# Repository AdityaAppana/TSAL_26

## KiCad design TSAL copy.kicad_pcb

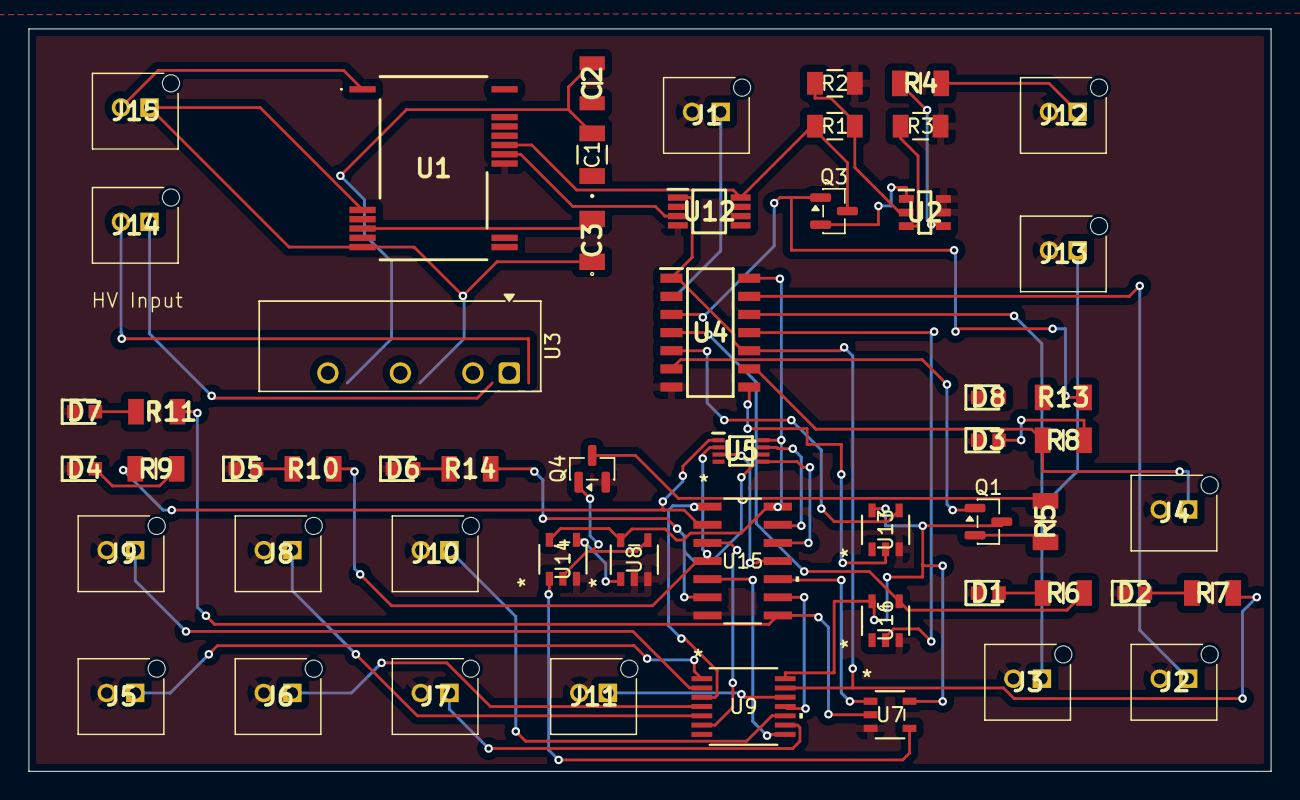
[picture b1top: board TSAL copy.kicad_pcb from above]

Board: 2 copper layers, 87.0 x 52.0 mm, 55 parts (0 on the bottom side), 58 nets.

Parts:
C1: 1u; 1206_AVX
C2: 100n; CAPC3216X95N
C3: 100p; C1206
D1, D2, D3, D4, D5, D6, D7, D8: LED; LEDC1608X70N
J1, J2, J3, J4, J5, J6, J7, J8, J9, J10, J11, J12, J13, J14, J15: Conn_01x02_Socket; B02BPASK1LFSN
Q1, Q3: AO3401A; SOT-23
Q4: AO3400A; SOT-23
R1: 976k; RC1206N_YAG
R2: 187k; RC1206N_YAG
R3: 191k; RC1206N_YAG
R4, R5, R6, R7, R8, R9, R10, R11, R13, R14: 1k; RESC3116X65N
U1: AMC0380R4; AMC0380R04DFXR
U2: LT6995-1; SOT95P280X100-6N
U3: TMA-0505S; Converter_DCDC_TRACO_TMA-05xxS_12xxS_Single_THT
U4: 74HC00; SOIC127P600X175-14N
U5: 74AHC2G00; SOP50P310X100-8N
U7: 74AHC1G08; DBV5
U8, U14: 74AHCT1G02; DBV5
U9: 74HC86; PW14
U12: TLV2372; SOP65P490X110-8N
U13, U16: 74AHC1G04; DBV5
U15: 74AHC04; D14

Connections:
+5V: Q3.3 (D), R1.1, U1.11 (REFIN), U1.14 (VDD2), U12.8 (V+)
GND: D1.1 (K), D2.1 (K), D3.1 (K), D4.1 (K), D5.1 (K), D6.1 (K), D7.1 (K), D8.1 (K), J1.2, J2.2, J3.2, J4.2, J5.2, J6.2, J7.2, J8.2, J9.2, J10.2, J11.2, J12.2, J13.2, Q4.2 (S), R2.2, R3.2, U1.9 (GND2), U2.5 (GND), U2.6 (RST), U4.7 (GND), U5.4 (GND), U7.3 (GND), U8.2, U8.3 (GND), U9.7 (GND), U12.4 (V-), U13.3 (GND), U14.3 (GND), U15.7 (GND), U16.3 (GND)
unnamed: D1.2 (A), R6.2
unnamed: D2.2 (A), R7.1
unnamed: D3.2 (A), R8.2
unnamed: D4.2 (A), R9.2
unnamed: D5.2 (A), R10.1
unnamed: D6.2 (A), R14.1
unnamed: D7.2 (A), R11.1
unnamed: D8.2 (A), R13.1
unnamed: J1.1, U4.2
unnamed: J2.1, U4.13
unnamed: J3.1, U4.12
unnamed: J4.1, R8.1, U4.9
unnamed: J5.1, U9.1
unnamed: J6.1, U9.4
unnamed: J7.1, U9.9
unnamed: J8.1, U9.5
unnamed: J9.1, U9.2
unnamed: J10.1, U9.10
unnamed: J11.1, U9.12
unnamed: J12.1, R4.2
unnamed: J13.1, Q4.3 (D), R5.2
unnamed: J14.1, U3.2 (-Vin)
unnamed: J14.2, U3.1 (+Vin)
unnamed: C1.1, C2.1, C3.1, J15.1, U1.2 (SNSC), U1.6 (GND1), U3.4 (-Vout)
unnamed: J15.2, U1.1 (HVIN)
unnamed: Q1.1 (G), U4.6
unnamed: Q1.2 (S), R5.1
unnamed: Q3.1 (G), R13.2, U4.3
unnamed: Q3.2 (S), U2.1 (V)
unnamed: Q4.1 (G), U8.4, U14.2
unnamed: R6.1, U4.4, U16.4
unnamed: R7.2, U4.1, U4.10, U9.13, U12.1
unnamed: R9.1, U5.1, U15.2
unnamed: R10.2, U5.2, U15.4
unnamed: R11.2, U7.2, U15.8
unnamed: R14.2, U5.6, U15.6
unnamed: U1.10 (OUT), U12.3 (+)
unnamed: C3.2, U1.4 (SNSP)
unnamed: C1.2, C2.2, U1.5 (VDD1), U3.6 (+Vout)
unnamed: R1.2, R2.1, U2.2 (DIV)
unnamed: R4.1, U2.4 (OUT)
unnamed: R3.1, U2.3 (SET)
unnamed: U4.8, U13.2
unnamed: U4.5, U13.4
unnamed: U7.4, U14.1
unnamed: U8.1, U14.4
unnamed: U9.3, U15.1
unnamed: U9.6, U15.3
unnamed: U9.8, U15.5
unnamed: U9.11, U15.9
unnamed: U7.1, U15.10
unnamed: U5.3, U15.11
unnamed: U5.5, U15.12
unnamed: U5.7, U15.13
unnamed: U4.11, U16.2
VCC: Q1.3 (D), U4.14 (VCC), U5.8 (VCC), U7.5 (VCC), U8.5 (VCC), U9.14 (VCC), U13.5 (VCC), U14.5 (VCC), U15.14 (VCC), U16.5 (VCC)

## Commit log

2026-06-02 Initial Kicad Commit
2026-06-28 AddedPullDown
